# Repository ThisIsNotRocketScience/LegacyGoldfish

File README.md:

# LegacyGoldfish
prototypes and proof-of-concept material used to develop the Goldfish

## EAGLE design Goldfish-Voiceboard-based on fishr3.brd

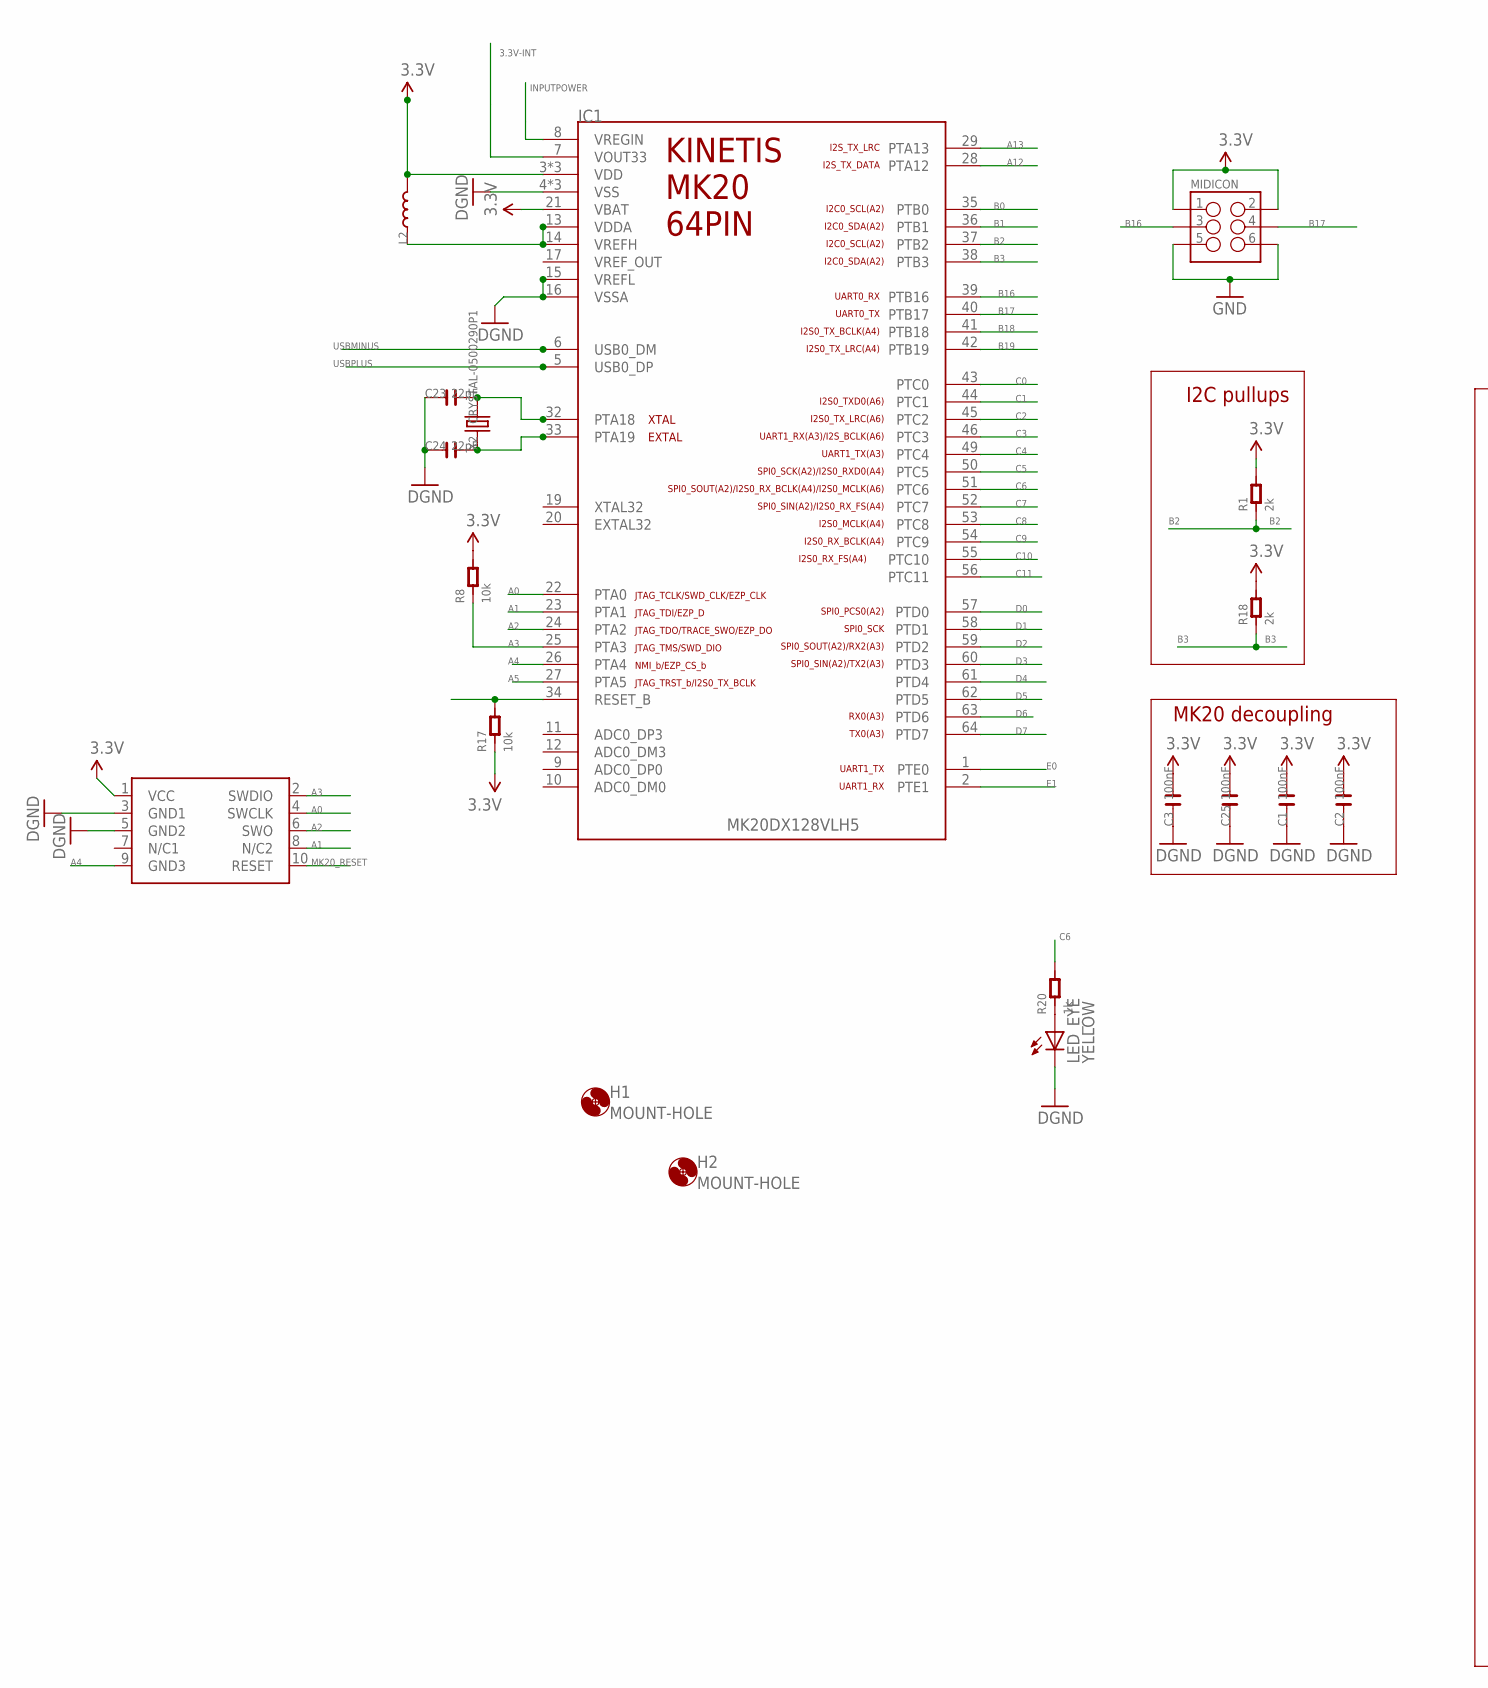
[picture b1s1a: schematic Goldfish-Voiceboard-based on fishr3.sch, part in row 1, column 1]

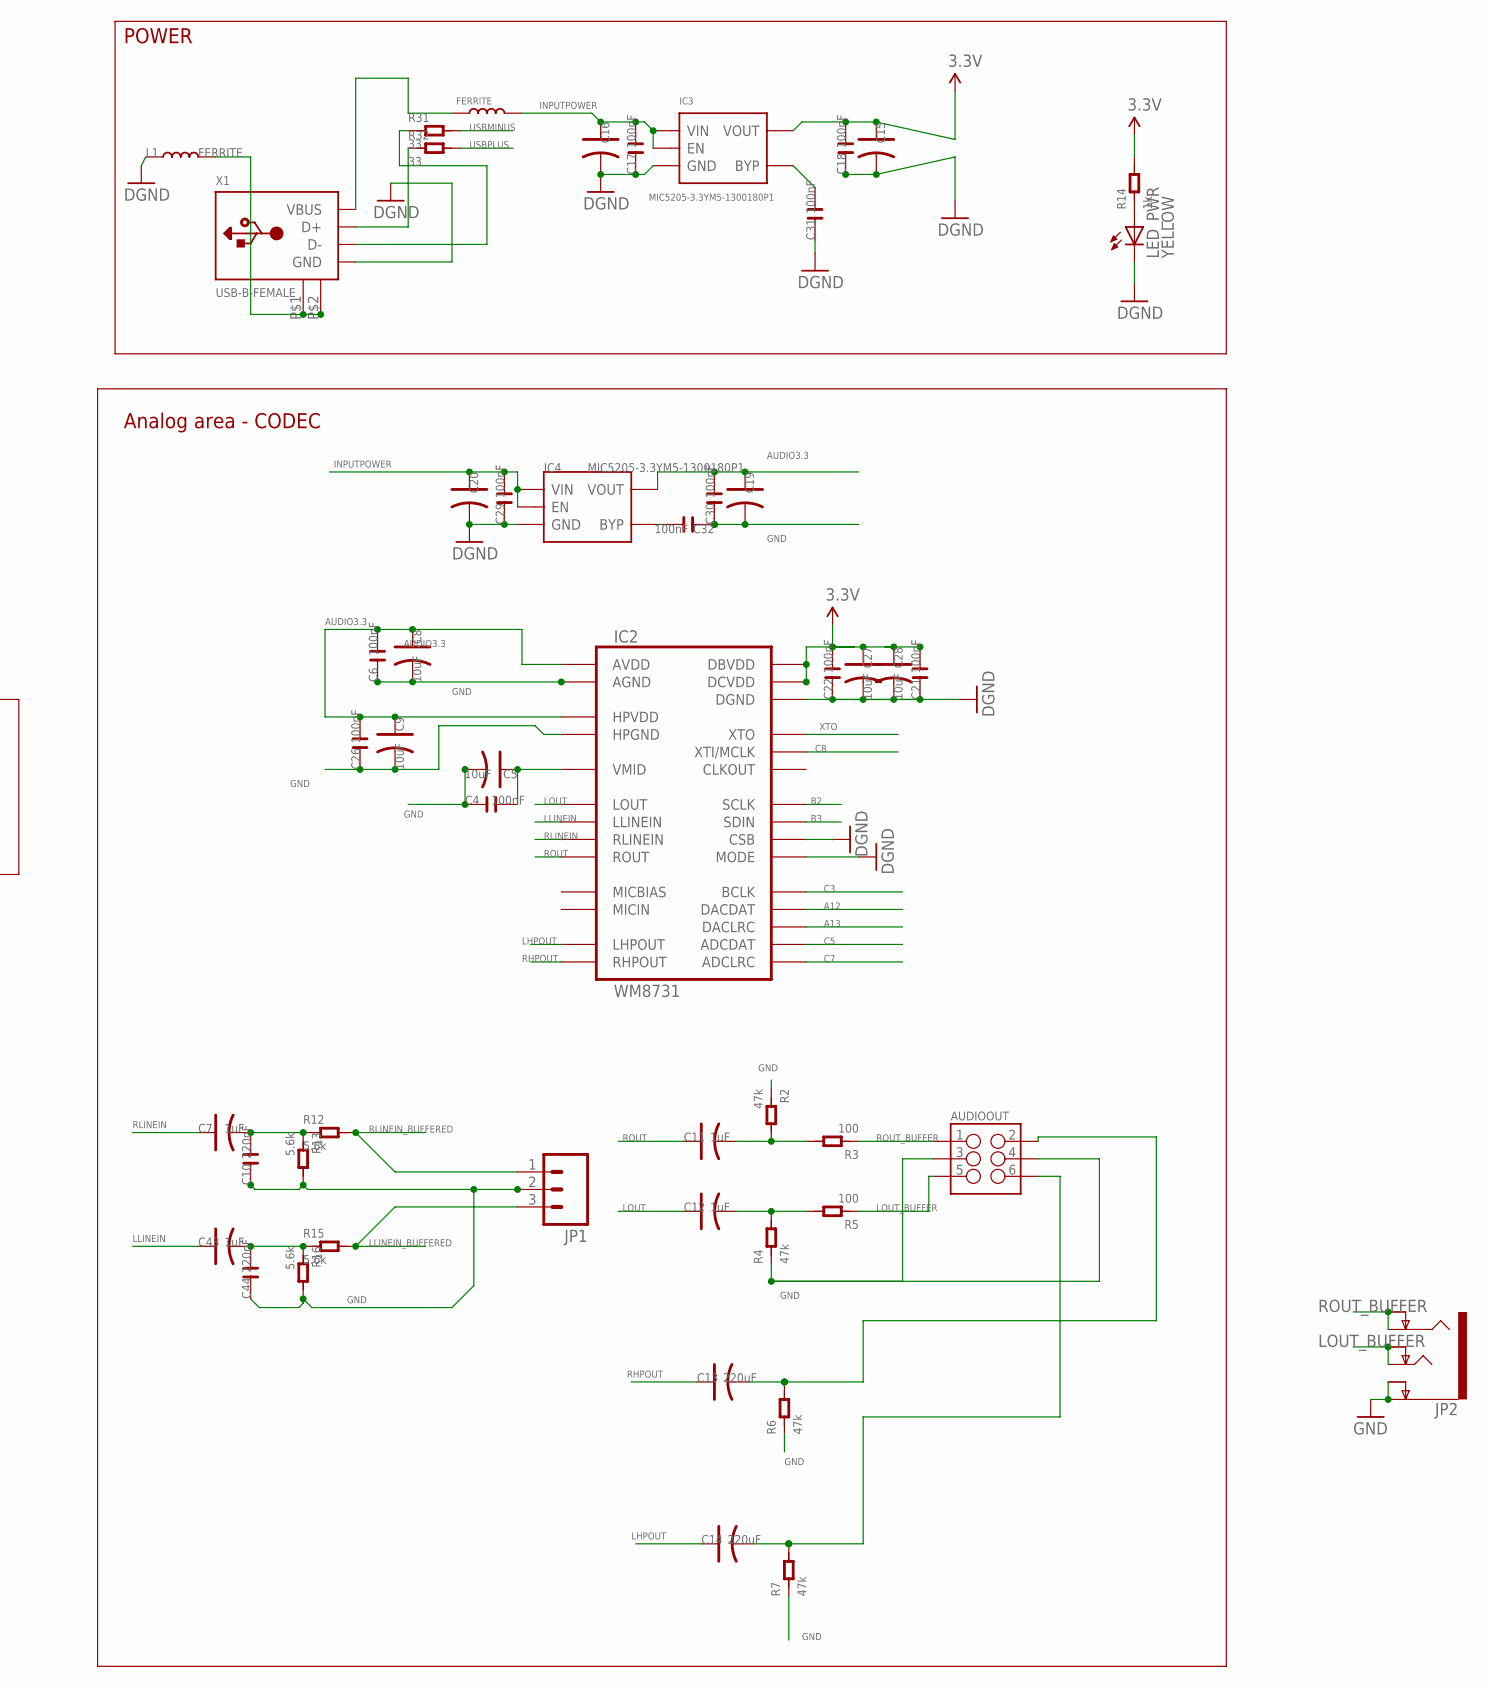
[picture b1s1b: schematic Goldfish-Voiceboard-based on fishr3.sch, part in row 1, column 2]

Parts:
AUDIOOUT: M03X2SMT; 2X3_SMT_POSTS
C1, C2, C3, C4, C6, C17, C18, C21, C22, C25, C26, C29, C30, C31, C32: 100nF; C0603
C5, C8, C9, C27, C28: 10uF; AVX-A
C7, C11, C12, C43: 1uF; AVX-A
C10, C44: 220nF; C0603
C13, C14: 220uF; AVX-B
C15, C16, C19, C20: C-POLAR-A; AVX-A
C23, C24: 22pF; C0603
H1, H2: MOUNT-HOLE; 3.2-NOMARKINGS-SMALLSAFEZONE
IC1: MK20DX128VLH5
IC2: WM8731; 28-SSOP
IC3, IC4: MIC5205-3.3YM5-1300180P1; SOT23-5
JP1: M03PTH; 1X03
JP2: AUDIO-JACK4-.25-HORIZ-TRS; AUDIO-JACK-.25-INCH-HORIZ-PTH
L1, L4: FERRITE; L0603
L2: L-0603; L0603
LED_EYE: YELLOW; CHIP-LED0603
LED_PWR: YELLOW; CHIP-LED0603
MIDICON: M03X2SMT; 2X3_SMT_POSTS
R1, R18: 2k; R0603
R2, R4, R6, R7: 47k; R0603
R3, R5: 100; R0603
R8, R17: 10k; R0603
R12, R13, R15, R16: 5.6k; R0603
R14, R20: 1k; R0603
R31, R32: 33; R0603
SWD1: CORTEX_SWD; M50-3600542
X1: USB-B-FEMALE; FCI61729
X2: CRYSTAL-0500290P1; 2P-SMD-5.0X3.2

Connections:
3.3V: C1.2, C2.2, C3.2, C15.+ (1), C18.2, C21.2, C22.2, C25.2, C27.+ (1), C28.+ (1), IC1.3 (VDD), IC1.21 (VBAT), IC1.30 (VDD), IC1.48 (VDD), IC2.P$1 (DBVDD), IC2.P$27 (DCVDD), IC3.5 (VOUT), L2.2, MIDICON.1, MIDICON.2, R1.2, R8.2, R14.2, R17.1, R18.2, SWD1.1 (VCC)
3.3V-INT: IC1.7 (VOUT33)
A0: IC1.22 (PTA0), SWD1.4 (SWCLK)
A1: IC1.23 (PTA1), SWD1.8 (N/C2)
A2: IC1.24 (PTA2), SWD1.6 (SWO)
A3: IC1.25 (PTA3), R8.1, SWD1.2 (SWDIO)
A4: IC1.26 (PTA4), SWD1.9 (GND3)
A5: IC1.27 (PTA5)
A12: IC1.28 (PTA12), IC2.P$4 (DACDAT)
A13: IC1.29 (PTA13), IC2.P$5 (DACLRC)
AUDIO3.3: C6.2, C8.+ (1), C9.+ (1), C19.+ (1), C26.2, C30.2, IC2.P$8 (HPVDD), IC2.P$14 (AVDD), IC4.5 (VOUT)
B0: IC1.35 (PTB0)
B1: IC1.36 (PTB1)
B2: IC1.37 (PTB2), IC2.P$24 (SCLK), R1.1
B3: IC1.38 (PTB3), IC2.P$23 (SDIN), R18.1
B16: IC1.39 (PTB16), MIDICON.3
B17: IC1.40 (PTB17), MIDICON.4
B18: IC1.41 (PTB18)
B19: IC1.42 (PTB19)
C0: IC1.43 (PTC0)
C1: IC1.44 (PTC1)
C2: IC1.45 (PTC2)
C3: IC1.46 (PTC3), IC2.P$3 (BCLK)
C4: IC1.49 (PTC4)
C5: IC1.50 (PTC5), IC2.P$6 (ADCDAT)
C6: IC1.51 (PTC6), R20.2
C7: IC1.52 (PTC7), IC2.P$7 (ADCLRC)
C8: IC1.53 (PTC8), IC2.P$25 (XTI/MCLK)
C9: IC1.54 (PTC9)
C10: IC1.55 (PTC10)
C11: IC1.56 (PTC11)
D0: IC1.57 (PTD0)
D1: IC1.58 (PTD1)
D2: IC1.59 (PTD2)
D3: IC1.60 (PTD3)
D4: IC1.61 (PTD4)
D5: IC1.62 (PTD5)
D6: IC1.63 (PTD6)
D7: IC1.64 (PTD7)
E0: IC1.1 (PTE0)
E1: IC1.2 (PTE1)
GND: AUDIOOUT.3, AUDIOOUT.4, C1.1, C2.1, C3.1, C4.1, C5.- (2), C6.1, C8.- (2), C9.- (2), C10.1, C15.- (2), C16.- (2), C17.1, C18.1, C19.- (2), C20.- (2), C21.1, C22.1, C23.1, C24.1, C25.1, C26.1, C27.- (2), C28.- (2), C29.1, C30.1, C31.1, C32.1, C44.1, IC1.4 (VSS), IC1.15 (VREFL), IC1.16 (VSSA), IC1.31 (VSS), IC1.47 (VSS), IC2.P$11 (HPGND), IC2.P$15 (AGND), IC2.P$21 (MODE), IC2.P$22 (CSB), IC2.P$28 (DGND), IC3.2 (GND), IC4.2 (GND), JP1.2, JP2.P$2 (EARTH), JP2.P$3 (EARTH-NORM), L1.1, LED_EYE.C, LED_PWR.C, MIDICON.5, MIDICON.6, R2.1, R4.1, R6.1, R7.1, R13.2, R16.2, SWD1.3 (GND1), SWD1.5 (GND2), X1.4 (GND)
INPUTPOWER: C16.+ (1), C17.2, C20.+ (1), C29.2, IC1.8 (VREGIN), IC3.1 (VIN), IC3.3 (EN), IC4.1 (VIN), IC4.3 (EN), L4.2
LHPOUT: C14.+ (1), IC2.P$9 (LHPOUT)
LHPOUT_BUFFER: AUDIOOUT.6, C14.- (2), R7.2
LLINEIN: C43.+ (1), IC2.P$20 (LLINEIN)
LLINEIN_BUFFERED: JP1.3, R15.2
LOUT: C12.+ (1), IC2.P$12 (LOUT)
LOUT_BUFFER: AUDIOOUT.5, JP2.P$6 (TIP), JP2.P$7 (TIP-NORM), R5.1
MK20_RESET: IC1.34 (RESET_B), R17.2, SWD1.10 (RESET)
unnamed: L4.1, X1.1 (VBUS)
unnamed: LED_PWR.A, R14.1
unnamed: L1.2, X1.P$1 (GND1), X1.P$2 (GND2)
unnamed: C23.2, IC1.32 (PTA18), X2.2
unnamed: C24.2, IC1.33 (PTA19), X2.1
unnamed: C31.2, IC3.4 (BYP)
unnamed: C32.2, IC4.4 (BYP)
unnamed: LED_EYE.A, R20.1
unnamed: IC1.13 (VDDA), IC1.14 (VREFH), L2.1
unnamed: C11.- (2), R2.2, R3.2
unnamed: C43.- (2), C44.2, R15.1, R16.1
unnamed: C7.- (2), C10.2, R12.1, R13.1
unnamed: C12.- (2), R4.2, R5.2
unnamed: C4.2, C5.+ (1), IC2.P$16 (VMID)
RHPOUT: C13.+ (1), IC2.P$10 (RHPOUT)
RHPOUT_BUFFER: AUDIOOUT.2, C13.- (2), R6.2
RLINEIN: C7.+ (1), IC2.P$19 (RLINEIN)
RLINEIN_BUFFERED: JP1.1, R12.2
ROUT: C11.+ (1), IC2.P$13 (ROUT)
ROUT_BUFFER: AUDIOOUT.1, JP2.P$4 (RING), JP2.P$5 (RING-NORM), R3.1
USBMINUS: IC1.6 (USB0_DM), R31.2
USBPLUS: IC1.5 (USB0_DP), R32.2
USB_N: R32.1, X1.3 (D+)
USB_P: R31.1, X1.2 (D-)
XTO: IC2.P$26 (XTO)

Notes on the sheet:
POWER
I2C pullups
MK20 decoupling
Analog area - CODEC

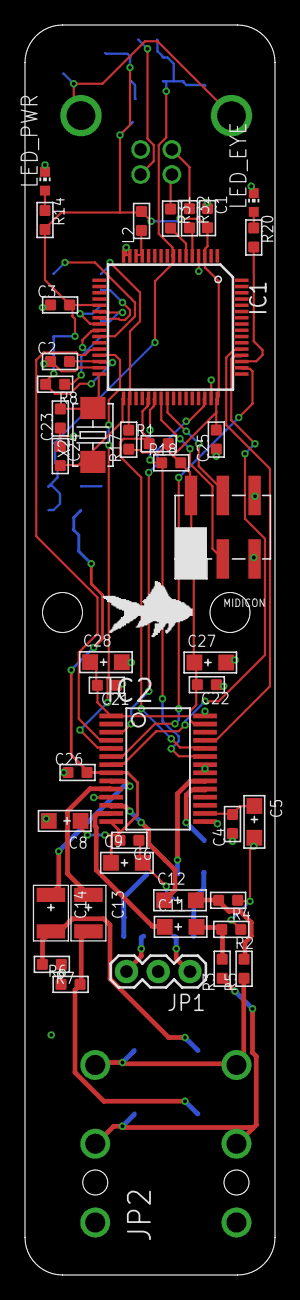
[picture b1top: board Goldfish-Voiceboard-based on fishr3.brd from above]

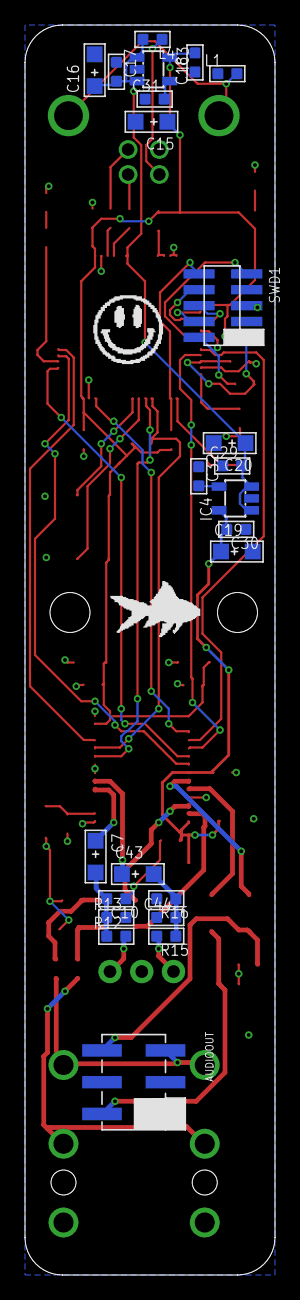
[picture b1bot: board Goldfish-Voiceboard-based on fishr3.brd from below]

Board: 2 copper layers, 20.0 x 100.0 mm, 73 parts (26 on the bottom side), 51 nets.

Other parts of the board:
U$1, U$3: FISH_SMALL
U$2: ACIDSMILE

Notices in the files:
parts and their libraries:
SparkFun-Connectors: Licensing: CC v3.0 Share-Alike You are welcome to use this library for commercial purposes.
